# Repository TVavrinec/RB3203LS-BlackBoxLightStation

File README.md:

# RB3203LS-BlackBoxLightStation

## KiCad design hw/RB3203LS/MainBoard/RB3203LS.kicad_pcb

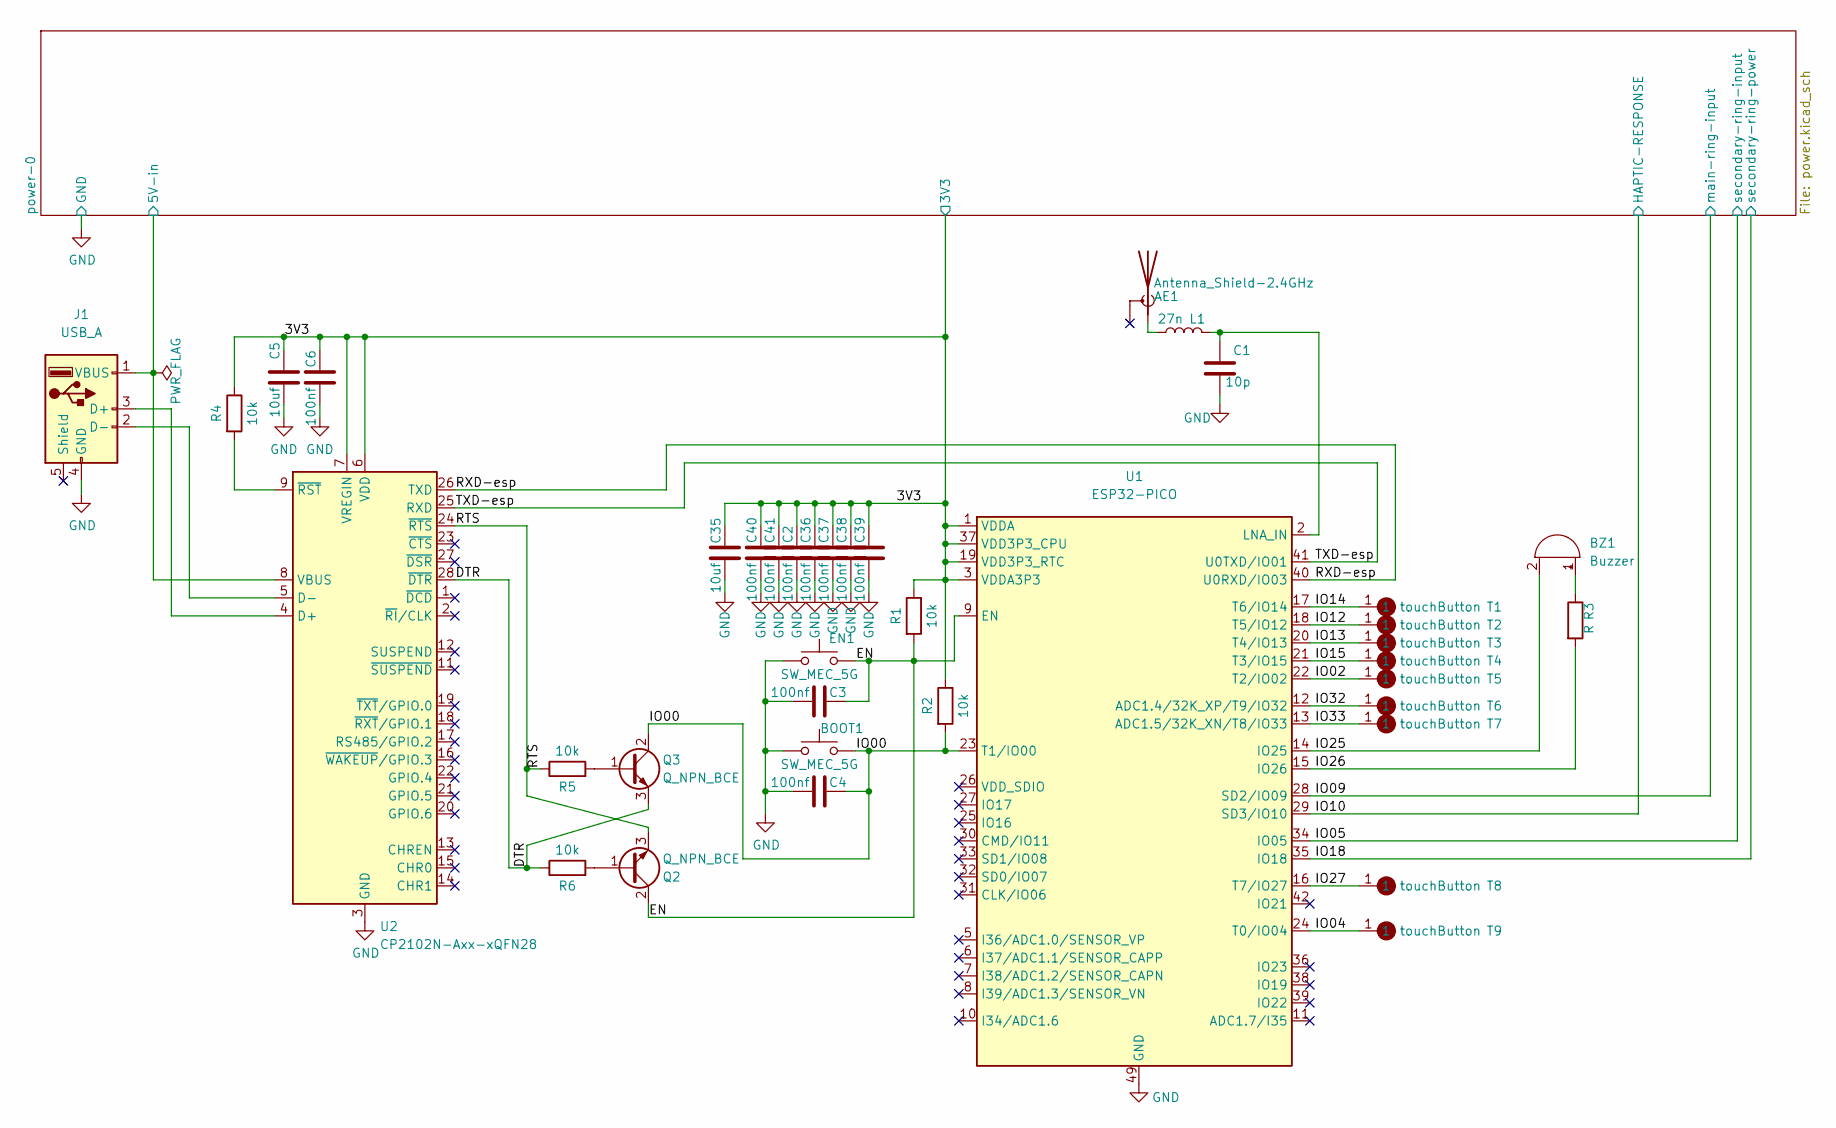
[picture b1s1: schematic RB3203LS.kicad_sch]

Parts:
AE1: Antenna_Shield-2.4GHz; SMD-2_1.6x3.1x0.6; LCSC C127629
BOOT1: SW_MEC_5G; SMD_3×4×2.0; PartNumber TS-1088-AR02016; LCSC C720477
BZ1: Buzzer; BUZ-SMD
C1: 10p; C_0402_1005Metric; LCSC C32949
C2, C3, C4, C6, C36, C37, C38, C39, C40, C41: 100nf; C_0402_1005Metric; PartNumber GCM155R71H104KE02D; LCSC C1525
C5, C35: 10uf; C_0402_1005Metric; PartNumber GRM155R61A106ME44D; LCSC C77000
EN1: SW_MEC_5G; SMD_3×4×2.0; PartNumber TS-1088-AR02016; LCSC C720477
J1: USB_A; USB-vertical
L1: 27n; L_0402_1005Metric; LCSC C90177
Q2, Q3: Q_NPN_BCE; SOT-23; LCSC C20526
R1, R2, R4, R5, R6: 10k; R_0402_1005Metric; PartNumber CRCW040210K0FKEDC; LCSC C25744
R3: R; R_0402_1005Metric
T1, T2, T3, T4, T5, T6, T7, T8, T9: touchButton; touch-point
U1: ESP32-PICO; QFN-48-1EP_7x7mm_P0.5mm_EP5.3x5.3mm
U2: CP2102N-Axx-xQFN28; QFN-28-1EP_5x5mm_P0.5mm_EP3.35x3.35mm

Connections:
/3V3: C2.1, C5.2, C6.1, C35.2, C36.1, C37.1, C38.1, C39.1, C40.1, C41.1, R1.1, R2.1, R4.1, U1.1 (VDDA), U1.3 (VDDA3P3), U1.4 (VDDA3P3), U1.19 (VDD3P3_RTC), U1.37 (VDD3P3_CPU), U1.43 (VDDA), U1.46 (VDDA), U2.6 (VDD), U2.7 (VREGIN); also elsewhere on the board
/DTR: Q3.3 (E), R6.1, U2.28 (~DTR)
/EN: C3.1, EN1.2 (B), Q2.2 (C), R1.2, U1.9 (EN)
/IO00: BOOT1.2 (B), C4.1, Q3.2 (C), R2.2, U1.23 (T1/IO00)
/IO02: T5.1, U1.22 (T2/IO02)
/IO04: T9.1, U1.24 (T0/IO04)
/IO05: U1.34 (IO05); also elsewhere on the board
/IO09: U1.28 (SD2/IO09); also elsewhere on the board
/IO10: U1.29 (SD3/IO10); also elsewhere on the board
/IO12: T2.1, U1.18 (T5/IO12)
/IO13: T3.1, U1.20 (T4/IO13)
/IO14: T1.1, U1.17 (T6/IO14)
/IO15: T4.1, U1.21 (T3/IO15)
/IO18: U1.35 (IO18); also elsewhere on the board
/IO25: BZ1.2 (+), U1.14 (IO25)
/IO26: R3.2, U1.15 (IO26)
/IO27: T8.1, U1.16 (T7/IO27)
/IO32: T6.1, U1.12 (ADC1.4/32K_XP/T9/IO32)
/IO33: T7.1, U1.13 (ADC1.5/32K_XN/T8/IO33)
/RTS: Q2.3 (E), R5.1, U2.24 (~RTS)
/RXD-esp: U1.40 (U0RXD/IO03), U2.26 (TXD)
/TXD-esp: U1.41 (U0TXD/IO01), U2.25 (RXD)
/power-0/VCC: J1.1 (VBUS), U2.8 (VBUS); also elsewhere on the board
GND: BOOT1.1 (A), C1.2, C2.2, C3.2, C4.2, C5.1, C6.2, C35.1, C36.2, C37.2, C38.2, C39.2, C40.2, C41.2, EN1.1 (A), J1.4 (GND), U1.49 (GND), U2.3 (GND), U2.29 (GND); also elsewhere on the board
unnamed: AE1.1 (A), L1.1
unnamed: BZ1.1 (-), R3.1
unnamed: C1.1, L1.2, U1.2 (LNA_IN)
unnamed: J1.2 (D-), U2.5 (D-)
unnamed: J1.3 (D+), U2.4 (D+)
unnamed: Q2.1 (B), R6.2
unnamed: Q3.1 (B), R5.2
unnamed: R4.2, U2.9 (~RST)

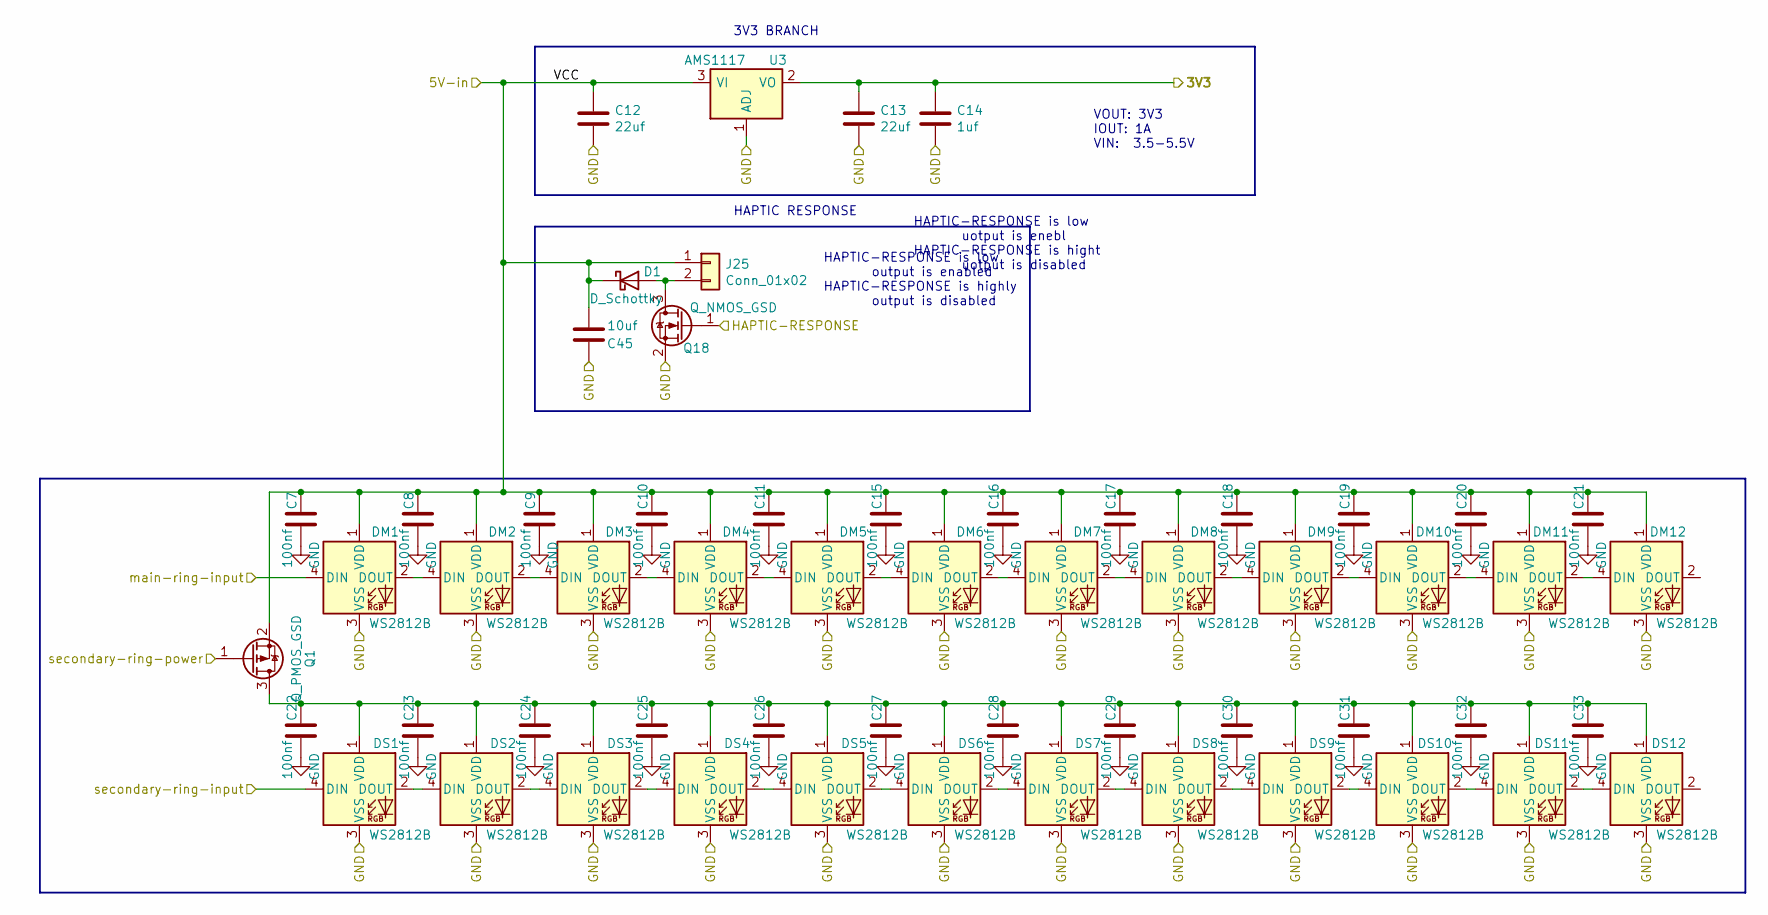
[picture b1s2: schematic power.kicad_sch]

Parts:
C7, C8, C9, C10, C11, C15, C16, C17, C18, C19, C20, C21, C22, C23, C24, C25, C26, C27, C28, C29, C30, C31, C32, C33: 100nf; C_0402_1005Metric; PartNumber GCM155R71H104KE02D; LCSC C1525
C12, C13: 22uf; C_0805_2012Metric; PartNumber CL21A226MAQNNNE; LCSC C45783
C14: 1uf; C_0805_2012Metric; PartNumber 885012207022; LCSC C28323
C45: 10uf; C_0402_1005Metric; PartNumber GRM155R61A106ME44D; LCSC C77000
D1: D_Schottky; SOD-882; PartNumber PMEG2005ELD,315; LCSC C458210
DM1, DM2, DM3, DM4, DM5, DM6, DM7, DM8, DM9, DM10, DM11, DM12: WS2812B; LED_WS2812B_PLCC4_5.0x5.0mm_P3.2mm
DS1, DS2, DS3, DS4, DS5, DS6, DS7, DS8, DS9, DS10, DS11, DS12: WS2812B; LED_WS2812B_PLCC4_5.0x5.0mm_P3.2mm
J25: Conn_01x02; SMD-pad-2x
Q1: Q_PMOS_GSD; SOT-23; PartNumber AO3401A; LCSC C15127
Q18: Q_NMOS_GSD; SOT-723; PartNumber PNM723T30V01; LCSC C169330
U3: AMS1117; SOT-223-3_TabPin2

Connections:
/3V3: C13.1, C14.1, U3.2 (VO); also elsewhere on the board
/IO05: DS1.4 (DIN); also elsewhere on the board
/IO09: DM1.4 (DIN); also elsewhere on the board
/IO10: Q18.1 (G); also elsewhere on the board
/IO18: Q1.1 (G); also elsewhere on the board
/power-0/VCC: C7.1, C8.1, C9.1, C10.1, C11.1, C12.1, C15.1, C16.1, C17.1, C18.1, C19.1, C20.1, C21.1, C45.2, D1.1 (K), DM1.1 (VDD), DM2.1 (VDD), DM3.1 (VDD), DM4.1 (VDD), DM5.1 (VDD), DM6.1 (VDD), DM7.1 (VDD), DM8.1 (VDD), DM9.1 (VDD), DM10.1 (VDD), DM11.1 (VDD), DM12.1 (VDD), J25.1, Q1.2 (S), U3.3 (VI); also elsewhere on the board
GND: C7.2, C8.2, C9.2, C10.2, C11.2, C12.2, C13.2, C14.2, C15.2, C16.2, C17.2, C18.2, C19.2, C20.2, C21.2, C22.2, C23.2, C24.2, C25.2, C26.2, C27.2, C28.2, C29.2, C30.2, C31.2, C32.2, C33.2, C45.1, DM1.3 (VSS), DM2.3 (VSS), DM3.3 (VSS), DM4.3 (VSS), DM5.3 (VSS), DM6.3 (VSS), DM7.3 (VSS), DM8.3 (VSS), DM9.3 (VSS), DM10.3 (VSS), DM11.3 (VSS), DM12.3 (VSS), DS1.3 (VSS), DS2.3 (VSS), DS3.3 (VSS), DS4.3 (VSS), DS5.3 (VSS), DS6.3 (VSS), DS7.3 (VSS), DS8.3 (VSS), DS9.3 (VSS), DS10.3 (VSS), DS11.3 (VSS), DS12.3 (VSS), Q18.2 (S), U3.1 (ADJ); also elsewhere on the board
unnamed: C22.1, C23.1, C24.1, C25.1, C26.1, C27.1, C28.1, C29.1, C30.1, C31.1, C32.1, C33.1, DS1.1 (VDD), DS2.1 (VDD), DS3.1 (VDD), DS4.1 (VDD), DS5.1 (VDD), DS6.1 (VDD), DS7.1 (VDD), DS8.1 (VDD), DS9.1 (VDD), DS10.1 (VDD), DS11.1 (VDD), DS12.1 (VDD), Q1.3 (D)
unnamed: D1.2 (A), J25.2, Q18.3 (D)
unnamed: DM1.2 (DOUT), DM2.4 (DIN)
unnamed: DM2.2 (DOUT), DM3.4 (DIN)
unnamed: DM3.2 (DOUT), DM4.4 (DIN)
unnamed: DM4.2 (DOUT), DM5.4 (DIN)
unnamed: DM5.2 (DOUT), DM6.4 (DIN)
unnamed: DM6.2 (DOUT), DM7.4 (DIN)
unnamed: DM7.2 (DOUT), DM8.4 (DIN)
unnamed: DM8.2 (DOUT), DM9.4 (DIN)
unnamed: DM10.2 (DOUT), DM11.4 (DIN)
unnamed: DM9.2 (DOUT), DM10.4 (DIN)
unnamed: DM11.2 (DOUT), DM12.4 (DIN)
unnamed: DS1.2 (DOUT), DS2.4 (DIN)
unnamed: DS2.2 (DOUT), DS3.4 (DIN)
unnamed: DS3.2 (DOUT), DS4.4 (DIN)
unnamed: DS4.2 (DOUT), DS5.4 (DIN)
unnamed: DS5.2 (DOUT), DS6.4 (DIN)
unnamed: DS6.2 (DOUT), DS7.4 (DIN)
unnamed: DS7.2 (DOUT), DS8.4 (DIN)
unnamed: DS8.2 (DOUT), DS9.4 (DIN)
unnamed: DS10.2 (DOUT), DS11.4 (DIN)
unnamed: DS9.2 (DOUT), DS10.4 (DIN)
unnamed: DS11.2 (DOUT), DS12.4 (DIN)

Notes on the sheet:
VOUT: 3V3 IOUT: 1A VIN: 3.5-5.5V
HAPTIC-RESPONSE is low uotput is enebl HAPTIC-RESPONSE is hight uotput is disabled
3V3 BRANCH
HAPTIC-RESPONSE is low output is enabled HAPTIC-RESPONSE is highly output is disabled
HAPTIC RESPONSE

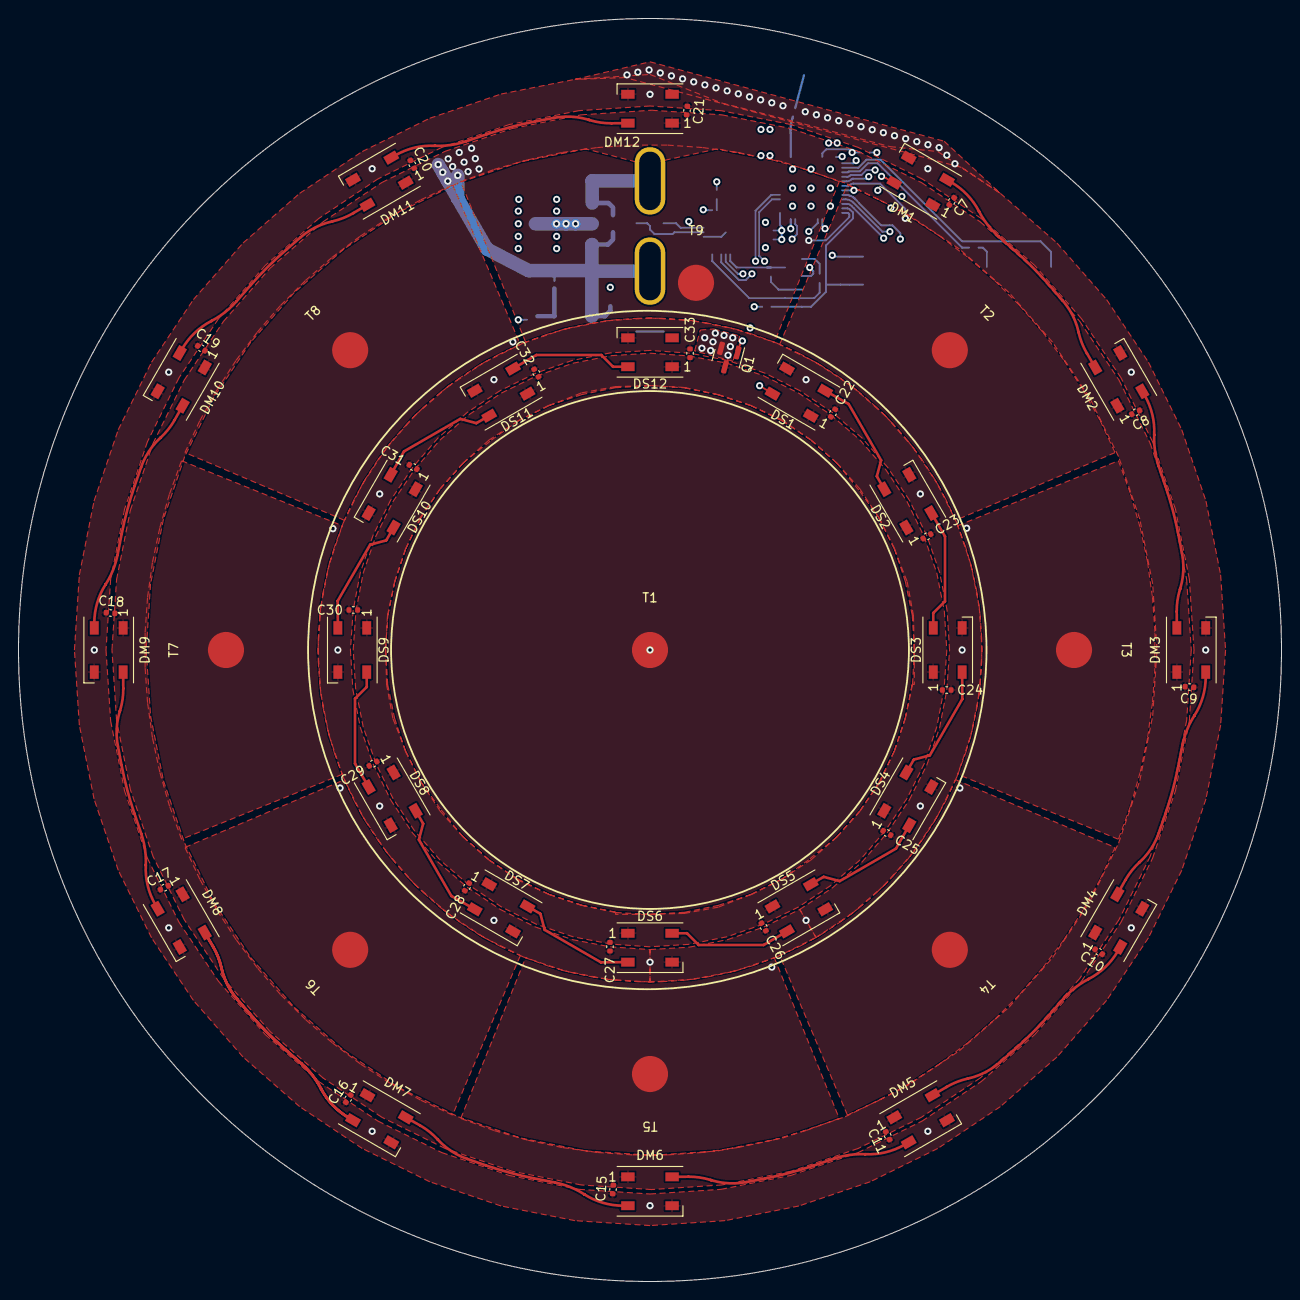
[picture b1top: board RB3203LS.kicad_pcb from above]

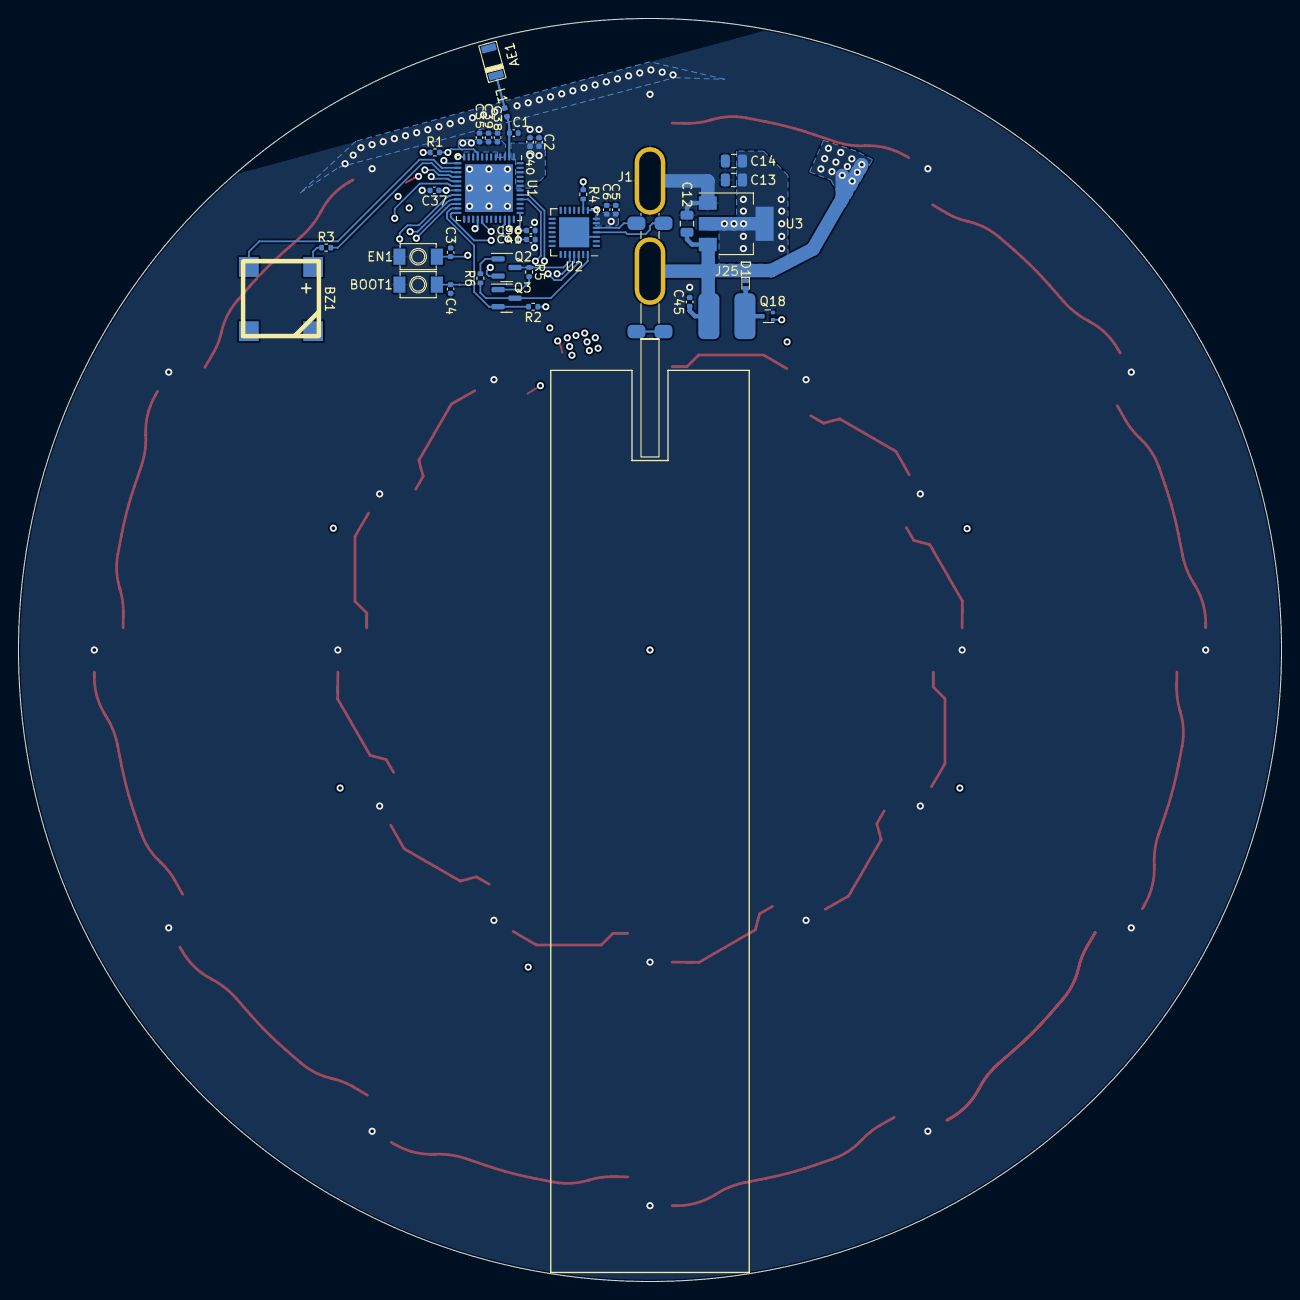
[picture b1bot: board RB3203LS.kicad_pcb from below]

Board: 4 copper layers, 140.0 x 140.0 mm, 95 parts (37 on the bottom side), 56 nets.

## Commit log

2022-08-01 RB3203LS-BlackBoxLightStation
